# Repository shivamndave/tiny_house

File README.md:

# tiny_house

This project is intended for the Micro-Grid Testbed Project and may be implemented
into The University of California at Santa Cruz's Tiny House Competition.

The subdirectories are as follows:
  - src:
    - firmware: (see examples and instructions below)
      - One-Wire Library: adds support for the temperature probe
      - UART-Library    : adds support for UART communication with the uC
      - Sensor_Driver   : a main driver for the project that includes an FSM for temperature control of a water heater
    - uC_Schematics:
      - several views of a PCB design that will house an AVR Atmega 328P uC that will be used as a controller for the driver
    - app:
      - tiny.html	: Basic frontend html page of the web application. Allows for displays of graphs
      - js		: Holds javascript source files, including the main date parser and JSON highchart files
        - lib		: Contains libraries used for the project, such as timepicker, for the date/time selection
      - css		: Styling for the frontend and media queres for responsive design. Also lib/jQuery stylesheets

	- FIRMWARE INSTRUCTIONS AND EXAMPLES
	
THIS FIRMWARE REPO IS INTENDED TO SERVE AS THE CONTROLLING SOFTWARE FOR A SMART REMOTE CONTROLLED WATER HEATER WITH VARIABLE SETPOINT, OFFSETS, AND MANIPULATEABLE STATES (DISABLE/ENABLE)

- TESTED ON AN ATMEGA2560, XBEE REV 2, AVR-GCC, AND AVR-DUDE USING AN ARDUINO PROGRAMER. CURRENTLY TESTING ON AN AVR ATMEGA 88PA-PU

- USART Library for serial I/O with the an AVR uC
	- formatted print functonality through uprintf()
- Dallas One Wire Library
	- Used for the temperature sensor probe and serial communication and floating point conversions for the sensor
GNU Makefile
	- supports builds with multiple source files, specify device, location, ISP model, and sources

DIRECTIONS FOR WIRELESS COMMUNICATIONS TRANSMISSION BAUDRATE = 19200

FRAME DETAILS:
	- 16-BIT ADDRESS
	- DEFAULT RECEIVER ADDRESS = 0x0001

CHECK COMMANDS LIST FOR AVAILABLE COMMANDS
APPEND THE DELIMITER DEFINED IN XBEE_LIB.h ~ 0x2D
	- EXAMPLE:
		- IN ORDER TO CHANGE THE SETPOINT TEMPERATURE TO 5 DEGREES CELSIUS
			- BYTE 1: 0xBB = CHANGE SETPOINT COMMAND --> COMMAND TO BE SENT
			- BYTE 2: 0x05 = 5 DEGREES CELSIUS --> ARGUMENT TO FIRST BYTE
			- BYTE 3: 0x2D = EOP -->'END OF PACKET' MESSAGE

- REPURPOSING INSTRUCTIONS
	- REDEFINE STATES IN main.c
	- REDEFINE THE PRIVATE driver LIBRARY FUNCTIONS FOR CORRECT REAL-WORLD OUTPUT
	- REDFINE STATE DEFINITIONS AND STRUCTURES IN fsm.h
	- REDEFINE SensorResult() IN driver.c/h TO PROVIDE THE CORRECT NEXT STATE

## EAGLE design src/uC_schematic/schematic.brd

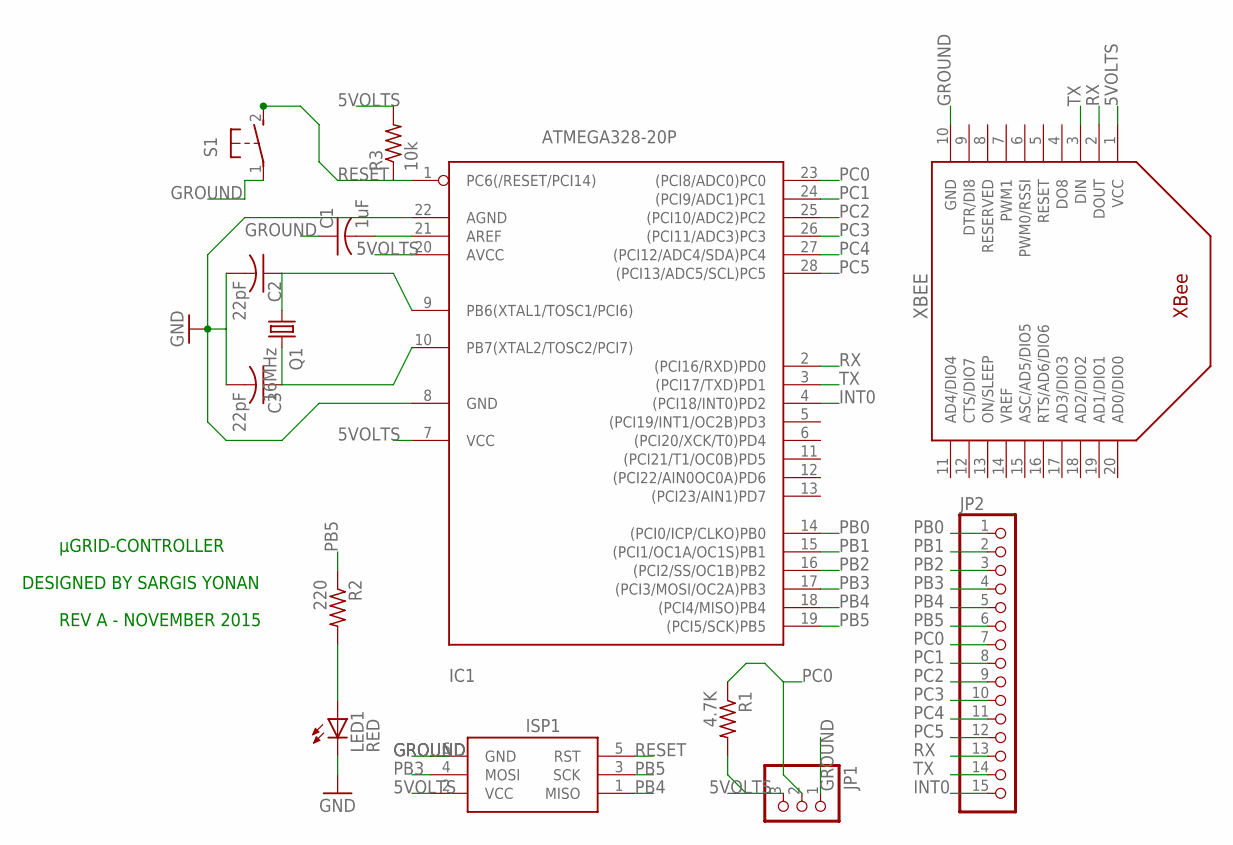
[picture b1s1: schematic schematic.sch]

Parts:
C1: 1uF; C025-024X044
C2, C3: 22pF; C025-024X044
IC1: ATMEGA328-20P; DIL28-3
ISP1: AVRISP-6; AVRISP
JP1: PINHD-1X3; 1X03
JP2: PINHD-1X15-CB; 1X15-CB
LED1: RED; LED3MM
Q1: 16MHz; HC18U-V
R1: 4.7K; 0204/7
R2: 220; 0204/7
R3: 10k; 0204/7
S1: 31-XX; B3F-31XX
XBEE: XBEE

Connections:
5VOLTS: IC1.7 (VCC), IC1.20 (AVCC), ISP1.2 (VCC), JP1.3, R1.2, R3.2, XBEE.1 (VCC)
GROUND: C1.1, C2.2, C3.2, IC1.8 (GND), IC1.22 (AGND), ISP1.6 (GND), JP1.1, LED1.K (C), S1.1, XBEE.10 (GND)
INT0: IC1.4 ((PCI18/INT0)PD2), JP2.15
unnamed: C1.2, IC1.21 (AREF)
unnamed: LED1.A, R2.2
unnamed: C2.1, IC1.9 (PB6(XTAL1/TOSC1/PCI6)), Q1.1
unnamed: C3.1, IC1.10 (PB7(XTAL2/TOSC2/PCI7)), Q1.2
PB0: IC1.14 ((PCI0/ICP/CLKO)PB0), JP2.1
PB1: IC1.15 ((PCI1/OC1A/OC1S)PB1), JP2.2
PB2: IC1.16 ((PCI2/SS/OC1B)PB2), JP2.3
PB3: IC1.17 ((PCI3/MOSI/OC2A)PB3), ISP1.4 (MOSI), JP2.4
PB4: IC1.18 ((PCI4/MISO)PB4), ISP1.1 (MISO), JP2.5
PB5: IC1.19 ((PCI5/SCK)PB5), ISP1.3 (SCK), JP2.6, R2.1
PC0: IC1.23 ((PCI8/ADC0)PC0), JP1.2, JP2.7, R1.1
PC1: IC1.24 ((PCI9/ADC1)PC1), JP2.8
PC2: IC1.25 ((PCI10/ADC2)PC2), JP2.9
PC3: IC1.26 ((PCI11/ADC3)PC3), JP2.10
PC4: IC1.27 ((PCI12/ADC4/SDA)PC4), JP2.11
PC5: IC1.28 ((PCI13/ADC5/SCL)PC5), JP2.12
RESET: IC1.1 (PC6(/RESET/PCI14)), ISP1.5 (RST), R3.1, S1.2 (S)
RX: IC1.2 ((PCI16/RXD)PD0), JP2.13, XBEE.2 (DOUT)
TX: IC1.3 ((PCI17/TXD)PD1), JP2.14, XBEE.3 (DIN)

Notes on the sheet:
DESIGNED BY SARGIS YONAN
REV A - NOVEMBER 2015
µGRID-CONTROLLER

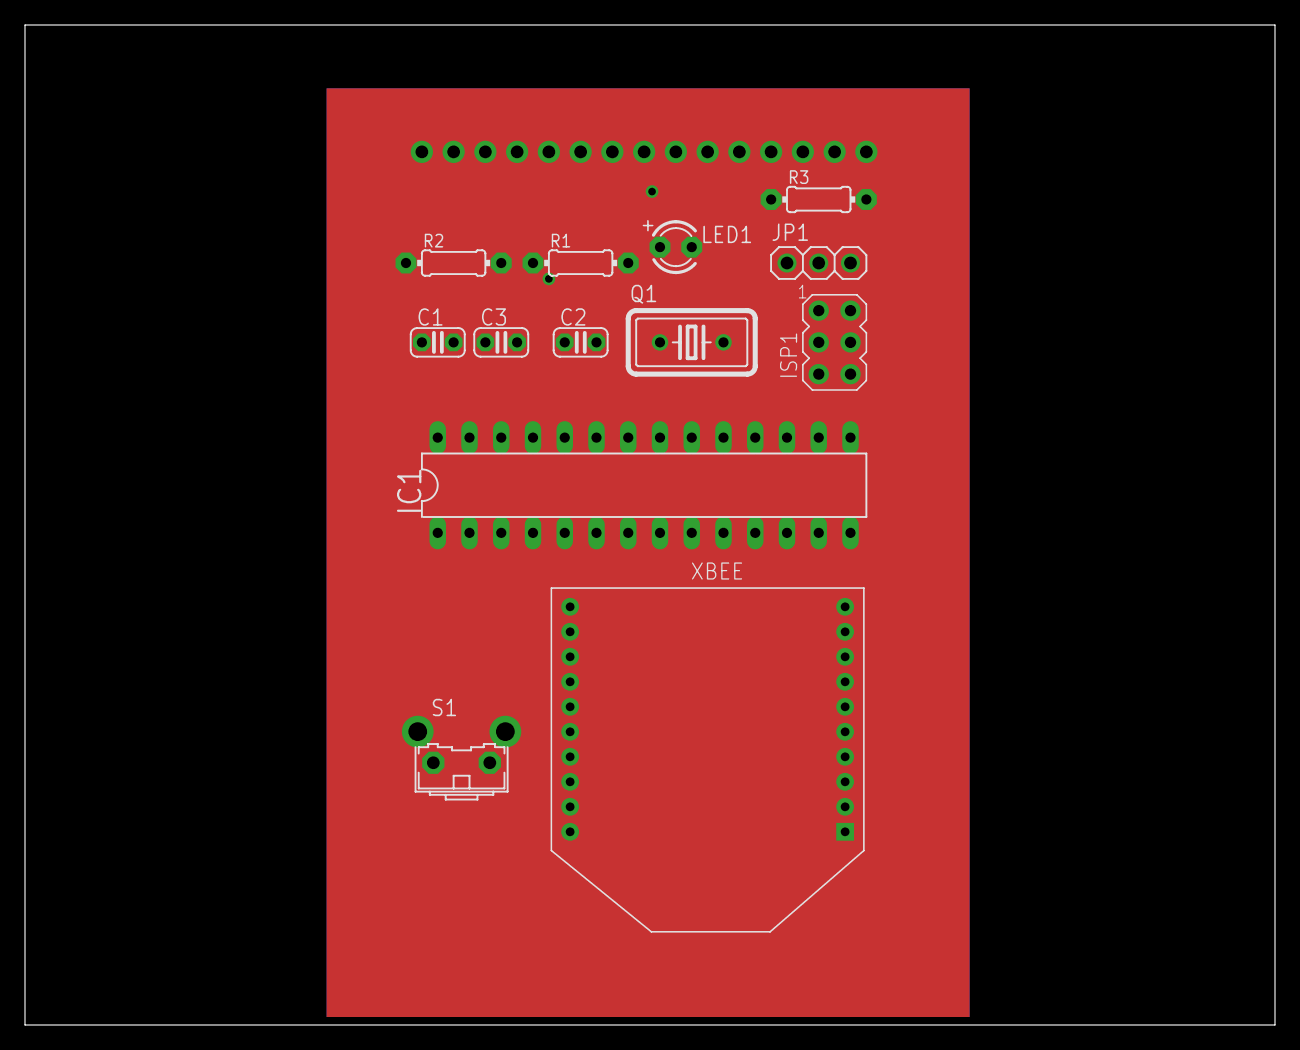
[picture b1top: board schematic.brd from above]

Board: 2 copper layers, 100.0 x 80.0 mm, 14 parts (0 on the bottom side), 22 nets.

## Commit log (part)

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2015-10-12 [Documentation] Intro Slides
    Uploaded original version of intro
    slides.
2015-10-12 [Documentation] Sprint 1 Plan
    Uploaded original revision/digital version
2015-10-12 [ADDITION] Added revision 1 of release plan
2015-10-12 Update Makefile
2015-10-13 I wrote a printf function for the uC to write through the uart
2015-10-18 I wrote a new GrabString Function, UARTGrabString, that receives a string from USART0. A driver program is in uprintf.c
2015-10-20 [Documentation] Sprint 1 Plan
    Revised to be upto date.
2015-10-21 Updated directory and build model
2015-10-21 sesnor driver directory added + driver header file
2015-10-23 adsf
    asdf
2015-10-23 Revert "adsf"
    This reverts commit 8c54bd3cee7a77f6dc52e004586fa49ec09b4fa9.
2015-10-26 [UI] Setup
    Added a main JS file and an index.html file
    setting up the dashboard files/directory.
2015-10-26 [UI] Setup
    Added a css style sheet to be used for styling.
2015-10-27 floating point working/dallas_type_to_float function working
2015-10-27 [UI] Setup RD
    Setup design to be responsive - as in the
    viewport will change width based on device.
    (Will implement media queries to have objects
    stack on small screens). However laid out grid frame
    with 2, 3, or 4 columns based on data being shown.
    Shows rough idea of how we may want to layout
2015-10-27 [UI] Menu/Header
    Switched the header info to the
    left and the 'menu' to the right.
2015-10-27 added F support for temperature
2015-10-28 finished FSM -- needs testing
2015-10-28 Removed .DS_STORE
2015-10-28 Revert "Frontend setup"
2015-10-29 working FSM
2015-11-14 removed all .ds_store files and banished them from this repo
2015-11-16 database directory
2015-11-18 bug fixes in xbee rx/tx
2015-11-18 testing xbee RX
2015-11-21 added more tests, modified grabCommand() to take uint8_t. figured out the garbled input issue
2015-11-21 [Reorganization]
    Removed extra/not needed/renamed files.
2015-11-21 [HTML]
    Redid html with reorganzized panels and
    ready for database setup.
2015-11-21 [CSS]
2015-11-21 [CSS]
    Removed header specific column css, changed
    to col format used by other cols.
2015-11-22 [Cleanup]
    Renamed sensor ids and changed header info dummy
    data.
2015-11-22 working rx/tx w/ commands
2015-11-23 Added remote feedback for testing
2015-11-23 added more testing for changing setpoint
2015-11-23 error case added
2015-11-23 [CSS]
    Moved leaded css styling files.
2015-11-23 [JS/JSON]
    Made base freqeuncy/power files.
2015-11-23 [JSON]
    Power json file made.
2015-11-23 [README]
2015-11-23 updated schematics
2015-11-24 xbee lib added
2015-11-25 xbee library updates
2015-11-25 commands - header gaurds added
2015-11-25 more modular FSM structure
2015-11-25 optimized in program size
2015-11-25 added rx frames
2015-11-26 added atmega88pa build system
2015-11-26 further optimization of c code
2015-11-27 fully optimized c code
2015-11-30 Database stuff
2015-11-30 [Files] Removed unneeded files.
2015-11-30 [Lib} Library files added for the time picker and the date picker.
2015-11-30 [CSS] Recommitting style.css file.
2015-11-30 [HTML]
    Renamed/adjusted tiny.html (main HTML file)
    to show charts.
2015-11-30 [LIB] Added library files.
2015-11-30 [HTML] Changed timepicker
    Adjusted time picker to use new lib format.
2015-11-30 Commented out header html
2015-11-30 Charts size changed to accomodate info.
2015-11-30 Adjusted setup of charts
2015-11-30 Reinitialized hide/show lists. Adjusted the charts to work for the correct temp
2015-11-30 Housekeeping actions, moved files around
2015-11-30 deleted some files
2015-11-30 renamed to be more according to CS115's specifications
2015-11-30 Sargis Yonan's Module Testing Report
2015-11-30 Moved the console logs, Also adjusted the timeparser to properly change the first colon to h in the api call URL.
2015-11-30 hardware and firmware installation guide added
2015-11-30 Shivam Dave Unit Module Testing file added.
2015-11-30 revised sprint 3 plan
2015-11-30 Added revision 1 of working prototypes & known problems report
2015-11-30 Added Sprint 3 Report
2015-11-30 updated report
2015-11-30 sargis' docs added
2015-11-30 [PHP]
    Edited the php file to take in new temperature set point values
    along with frequency and checks in the mysql query for info_id
2015-12-01 Added installation guide for frontend/database
2015-12-01 Renamed installation guide
2015-12-01 Moved System Test Scenarios doc
2015-12-01 Known Problems doc added
2015-12-01 refactored repo
2015-12-01 refactored rx protocol comment
2015-12-01 fixed commands bug
2016-01-23 push test
2016-01-26 comment issue while compiling for mega
2016-01-26 works on mega with new commands
2016-03-08 Added a gitignore for db_credentials
2016-03-08 Live.php finally pushed up, current version works for old db schema, will be retrofitted for new one
2016-03-09 Added in actuator/sensor data retireval and other information. REQUIRES TESTING.
2016-03-09 Made values an array of values instead of last value
2016-03-09 dateSetter latest stable version that shows latest setpoint as vertical bar
2016-03-09 Updated initial data and setpoint getter
2016-03-09 Fixed default sensor data for the general sensor chart
2016-03-09 Sensor/Equipment Info added:
    Added back jQuery calls to showcase equipment and sensor information
    in addition to the actuator setpoint that is actively updated based on setpoint
    changes.
2016-03-22 Redesign old html, used for demo
    Was made nicer and color coordinated, with color changes and bootstrap
    organizing
2016-03-22 Added redesign file for the redesign of web page
2016-03-22 This is just a test commit
2016-03-26 Moved the display setup files
2016-03-26 Removed unused display files
2016-03-26 moved template/home html
2016-03-26 Moved data controllers
2016-03-27 Mobile related adjustments to chart size/etc
2016-03-27 Added status query
2016-03-27 Changed to bootstrap gridsystem
2016-03-27 [UPDATED]
    Fixed the files so they have the most updated code. Also,
    fixed routes so they point to correct files.
2016-03-27 Moved common folder a bit to add common/controllers
2016-03-27 Removed /databases/.DS_Store
2016-03-28 Added db_credentials sample
2016-03-29 More live.php comments
    Completed commenting the file
2016-03-29 Update README.md
    Added README information
2016-03-29 Update README.md
    Added more descriptions regarding backend. File descriptions finished for API.
2016-03-29 Update README_livephp.md
    Adjusts ordering to be more intuitive
2016-03-29 Update date_setter_color.js
    Added comments
2016-03-29 Update setupSetptDisplay.js
    Adjusted comments
2016-03-29 Update README.md
    Added URL request information
2016-04-03 Added bower.json
2016-04-03 Moved tiny_color.html over to the bower_components
2016-04-03 Images re-added and removed unused lib
2016-04-03 Added angular controllers and made a test home page
2016-04-03 Fixed index merge to use controllers
2016-04-13 Sass
2016-04-13 Sets up the homepage and main controller
2016-04-27 JQuery files updated and added to bower
2016-04-27 Updated node_modules file
2016-04-27 HomeController Formatted for Angular
    This is the updated home page with angular. It currently dynamically updates the
    front page using a directive for the displays. Actuator displays will be implemented next
    . Also planning on making it more robust, however this is the home page conversion we want
2016-04-27 [Home]
    home.html has been formatted to populate the page
    with displays based on data gotten from the database
2016-05-06 Changed .gitignore for the Python api incoming
2016-05-06 Extra css files updated
2016-05-06 Remove old api
2016-05-06 [API] Flask api
    Flask API added to the folder so that it works similar to before
    however on a simple /API url. Next this url will be expanded upon.
    Also added a .wsgi file for the app so tht apache support for the vm
    is added.
2016-05-06 Change to use new slightly changed api url
2016-05-11 Fixed issue with pulling room info and status
2016-05-12 Initial addition of Commands controller and page
2016-05-12 Added commands page to route
2016-05-13 Added functionality to select room by id in API and check for None type
2016-05-13 [getDataService]
    getDataService is not a global app service. So it can be used
    from any controller.
2016-05-13 Cancels interval on changing the page
2016-05-13 Added nav bar across app
2016-05-13 Added onboard to menu at top
2016-05-14 [Onboard Form]
    Add a placeholder onboard form that will get
    mqtt message data
2016-05-20 These commits include: A whole new nav bar, new css styling for the web page, bugs and glitches are fixed in the sensors page, modularity with three of the pages is around 95% complete
2016-05-20 Files changed from merge
2016-05-20 Changes from merge
2016-05-20 Updated scan button and added repeat of the form for each sensor
2016-05-20 Added equipment query to api
2016-05-20 Changed form to white text and added onboard to menu
2016-05-20 html web page size bug was fixed by editing the css class called body in the btnlib
2016-05-20 page refresh bug when user menu was selected was fixed by removing a needless href in teh html
2016-05-26 Added a function and query for getting just mac addresses of equipment.Returns of current equipment mac addresses in a list
2016-05-26 Request needed in flask
2016-05-26 [Onboard]
    Added service to post a new sensor to the database, calls
    our api to post a new sensor and equipment if new
2016-05-26 [Onboard]
    Sets default scope variables in the form based on query and
    passed in data from the mqtt call previously made. Also creates the
    JSON variable that will be posted on clicking submit.
2016-05-27 Removed additional room query and such. Defaults new equipment to default first room. This allows quick addition of new equipment/sensor pairings. Also removed additional/unneeded queries/form inputs.
2016-05-27 adding in new libs
2016-05-27 Added send command service
2016-05-27 Uses mqtt command service instead of programmed here
2016-05-27 Fixed uid's for sensors, now are appropriate and match commands
2016-05-27 Actuation placeholder info passed to database through variable
2016-05-27 Added command for a light sensor
2016-05-27 Added service that will setup a chart
2016-05-27 [Onboard] Bug
    Fixed bug where not all sensors passed into sensor_array for onboarding. Now
    we use a scope variable to keep track of the array
2016-05-27 Removed unneeded log
2016-05-28 Knobs added to dashboard
2016-05-28 Moved onboard controller service to controller
2016-05-28 Added buttons based on types of sensor/actuators used
2016-05-28 Added setpoint test functions/buttons that send a new datapoint to the database. This is setup for reza's setpoint knob
2016-05-28 Unneeded file
2016-05-28 Added all needed buttons for all light sensor commands
2016-05-28 Knob.js scrolling glitch fixes
2016-06-02 API
    Make queries for a specific equipment piece
2016-06-02 API
    Actuator queries added. Able to query for all or specific, similar to
    sensors
2016-06-02 Settings
    Changed settings page to accomodate settings page and angular-ui
    lib. Also nav bar adjusted for settings button
2016-06-02 Settings
    Settings HTML pages added for all sensors and specific sensors
2016-06-04 API
    Fixed the actuator API call's sensor_info. Now not a one element array
2016-06-04 API
    All settings page update calls added to adjust necessay info for a
    room, sensor, actuator and equipment.
2016-06-04 Service
    Added general post to database service that can be used by all
    controllers
2016-06-04 Settings
    Post data pass to API call for each settings sepcific page.
2016-06-04 Settings
    Actuator settings html page
2016-06-04 Settings
    Html rooms page adjusted for proper postData
2016-06-04 Settings
    Html sensors page adjusted for proper postData
